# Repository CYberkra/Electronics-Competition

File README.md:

# AWG K325T — 任意波形信号发生器

> 第二十一届研电赛 · 优利德赛题二 FPGA 数字基带
> 目标器件：Xilinx Kintex-7 XC7K325TFFG900-2（正点原子 K7-325T）
> 子卡：FMCADDA-9250-9144 (AD9144 DAC)
> 扩展模块：KiCad PCB (ST7789 LCD + EC11 编码器 + Logo 丝印)

---

## 项目简介

基于 **K7-325T** + **AD9144 DAC** 的高速任意波形发生器，TX-only 纯信号生成设计。

### 核心指标

| 指标 | 值 | 赛题要求 |
|------|----|---------|
| DAC | AD9144, 4ch 16bit, 2.8Gsps | ≥5GSa/s ⚠️ |
| 垂直分辨率 | 16 bit | ≥14bit ✅ |
| 频率分辨率 | 48bit DDS, ~μHz | ≤1mHz ✅ |
| JESD204B | TX 4L @10Gbps | — |
| 时钟 | LMK04828 (50M TCXO) | — |
| 控制 | UART 115200 + 按键 | — |

### 实测幅度 (2026-06-14, 满幅度 0x7FFF)

| 100kHz | 1MHz | 10MHz | 100MHz | 300MHz |
|--------|------|-------|--------|--------|
| 60mV | 120mV | 500mV | 680mV | 470mV |

### 频谱仪频域测试 (2026-06-16, 满幅度 0x7FFF)

| 指标 | 赛题要求 | 实测值 | 结果 |
|------|----------|--------|:--:|
| 谐波失真 (100MHz) | < -40 dBc | **-54.9 dBc** | ✅ |
| 带内平坦度 (10~300MHz) | < 3 dB | **2.6 dB** | ✅ |
| 线性扫频 (10~100MHz) | 支持 | 10 峰等间距 | ✅ |
| 对数扫频 (1~128MHz) | 支持 | 8 峰倍频程 | ✅ |

### 当前进度

- [x] JESD204B 4L @10Gbps 建链
- [x] LMK04828 SPI 时钟配置
- [x] SPI clock-enable 重构 (derived clock → clk_in + spi_tick)
- [x] DDS 4级流水线 (48bit, 4采样/周期, Sine LUT 4096×16bit)
- [x] 4种波形 (正弦/方波/三角/锯齿) + BRAM 任意波形
- [x] 扫频引擎 (线性 + 对数, sweep_engine.v)
- [x] SFCW/对数扫频寄存器 (0x50-0x6C) + FMCW chirp 模式
- [x] 幅度/偏置 Q1.15 缩放
- [x] 数字校准表实例化 (ad9144_awg_cal, BRAM 16bin 频率补偿)
- [x] UART 远程控制 (115200 8N1 ASCII 协议)
- [x] 板载按键控制 (KEY0/KEY1)
- [x] KiCad 扩展模块 (ST7789 + EC11, 含 Logo 丝印)
- [x] 竞赛文档 (设计文档 + 测试方案 + PPT)
- [x] EC11 FPGA 驱动 (正交解码 + 消抖 + AWG 桥接)
- [x] ST7789 FPGA 驱动 (SPI 驱动 + 字符渲染 + 菜单系统)
- [x] 频谱仪频域测试 (谐波失真 -54.9dBc, 平坦度 2.6dB)
- [ ] 外部放大器 (→3Vpp)
- [ ] TFT/EC11 上板验证 (PCB 物理问题待排查)

---

## 环境要求

| 项目 | 版本/路径 |
|------|----------|
| **Vivado** | **2024.1** (2024.2+ 无 7 系 JESD IP) |
| 目标器件 | `xc7k325tffg900-2` |
| License | Synthesis + JESD204 |

---

## 快速开始

### 构建 & 烧录

```powershell
# 综合 → 实现 → Bitstream
& D:\Xilinx\Vivado\2024.1\bin\vivado.bat -mode batch -source scripts/build_all.tcl

# 烧录
& D:\Xilinx\Vivado\2024.1\bin\vivado.bat -mode batch -source scripts/program.tcl
```

### UART 控制

```python
python tools/set_freq.py 50000000  # 50MHz
# 或手动: W 08 00000003 (开控制) → W 10/14 (设频率) → W 2C 00000001 (应用)
```

---

## 仓库结构

```
Electronics-Competition/
├── rtl/               # Verilog RTL (top/ control/ dds/ dsp/ jesd/ sweep/ wave/)
├── constraints/       # XDC 约束 (awg_k325t.xdc, fmc_adda.xdc)
├── vivado/            # Vivado 工程
├── docs/tasks/        # 开发任务文档 (SFCW, GUI)
├── scripts/           # Tcl 构建/烧录脚本
├── tools/             # Python UART 工具
├── docs/competition/  # 竞赛文档 (设计文档/测试方案/PPT/视频脚本)
├── sim/               # 仿真 testbench
└── kicad/             # KiCad 扩展模块 PCB
```

## 扩展模块管脚

| 功能 | FPGA 引脚 | 备注 |
|------|----------|------|
| TFT SPI (6pin) | N27/M24/M27/M25/N29/M20 | ST7789, P2 CMOS接口 |
| EC11 编码器 | L20/J21/J22 | CMOS_D1/D2/D3 |
| LEDK | L30 | CMOS_D4 |

约束已备注释在 `constraints/awg_k325t.xdc` §14，顶层端口待加。

---

## 关键文档

| 需求 | 位置 |
|------|------|
| 赛题原文 (官方PDF) | `docs/references/研电赛第21届技术竞赛赛题清单.pdf` |
| 赛题原文 (文本) | `docs/competition/uni-trend-problem-statement.md` |
| 设计文档 | `docs/competition/design_document.md` |
| 测试方案 | `docs/competition/AWG指标测试方案.md` |
| 测试记录 | `docs/competition/AWG指标测试结果记录.md` |
| 答辩 PPT | `docs/competition/竞赛答辩PPT.pptx` |
| PPT 大纲 | `docs/competition/答辩PPT内容大纲.md` |
| 视频脚本 | `docs/competition/video_script.md` |
| 技术论文 | `docs/competition/技术论文.md` |
| 交付物清单 | `docs/competition/交付物清单.md` |
| 扩展模块管脚 | `kicad/模块管脚分配表.csv` |
| SFCW/FMCW 任务 | `docs/tasks/SFCW_FMCW_波形生成任务.md` |
| TFT+EC11 GUI 任务 | `docs/tasks/TFT_Encoder_GUI_菜单系统任务.md` |

---

> **最后更新**: 2026-06-15

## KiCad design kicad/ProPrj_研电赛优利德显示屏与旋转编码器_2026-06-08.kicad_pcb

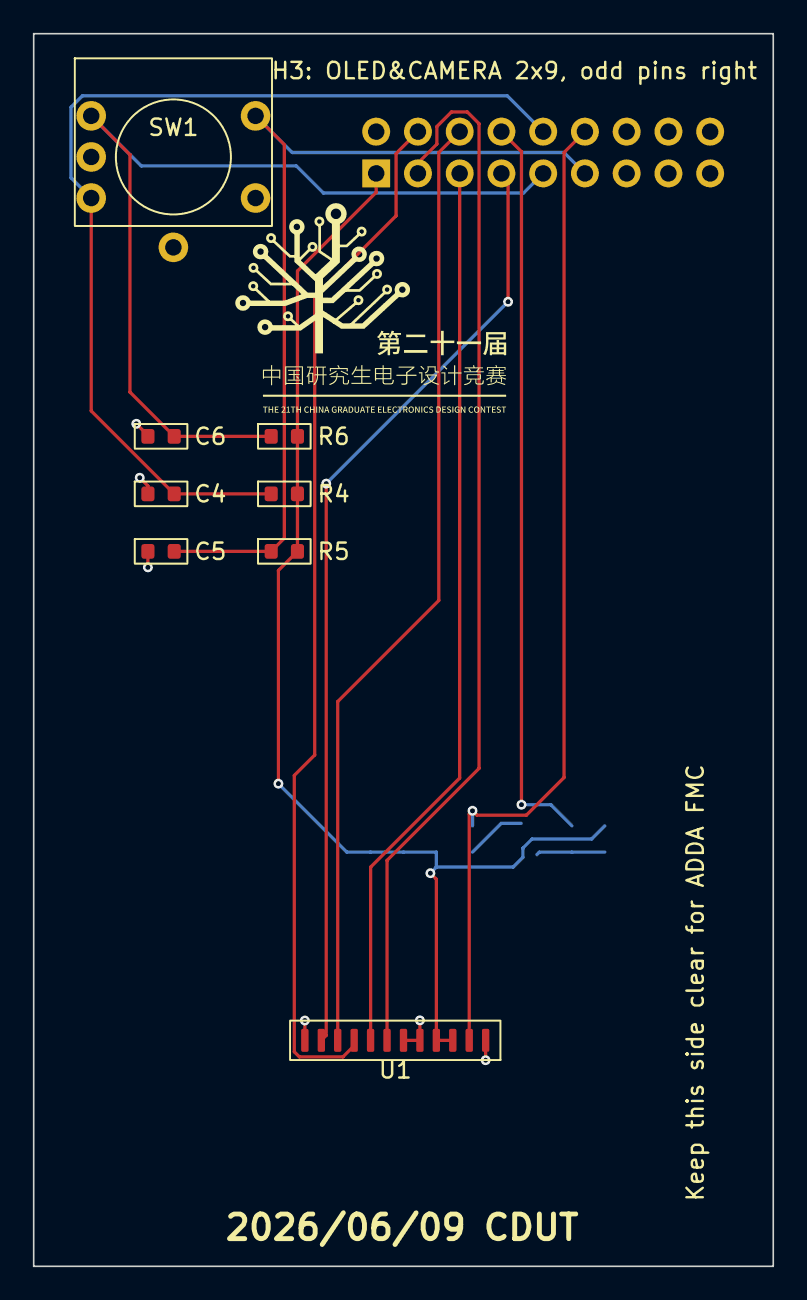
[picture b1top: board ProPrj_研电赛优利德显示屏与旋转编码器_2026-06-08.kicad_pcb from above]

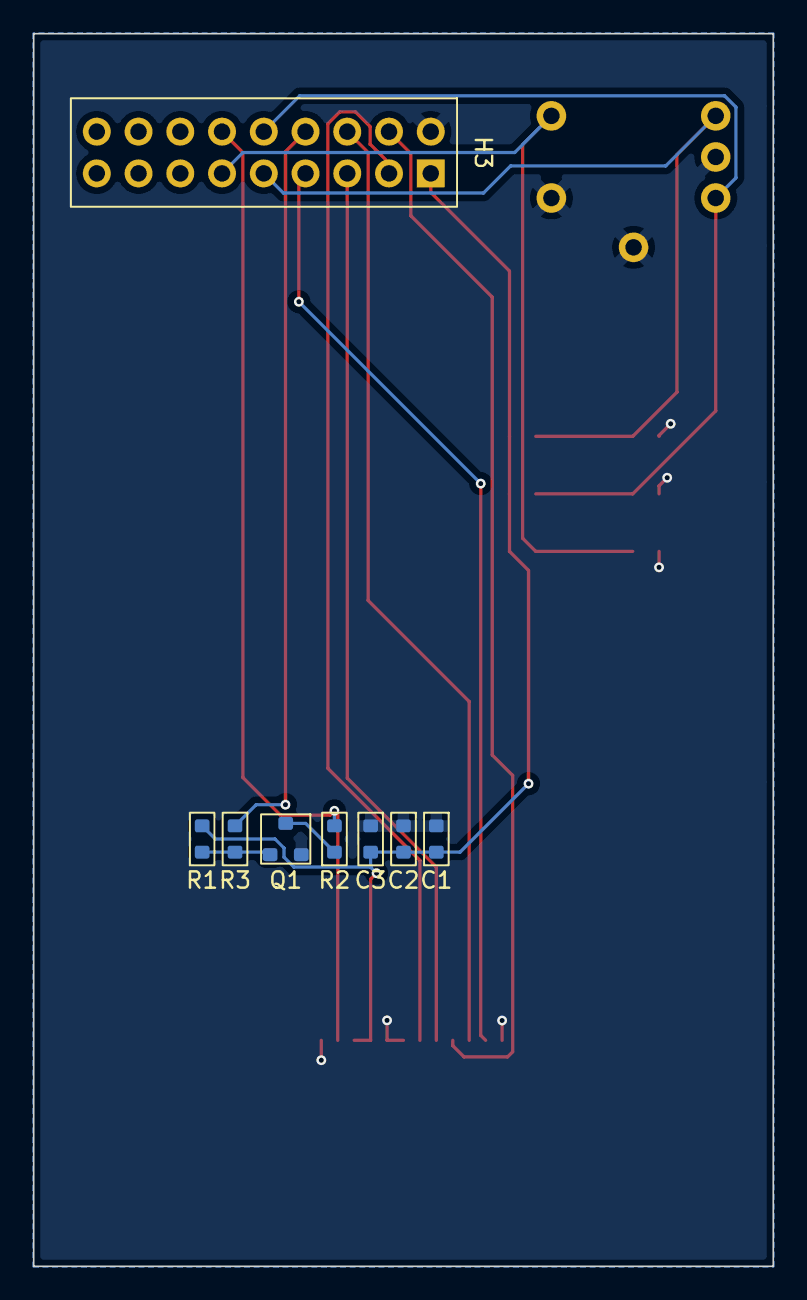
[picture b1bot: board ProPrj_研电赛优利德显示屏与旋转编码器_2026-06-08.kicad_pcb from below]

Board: 2 copper layers, 45.0 x 75.0 mm, 16 parts (8 on the bottom side), 14 nets.

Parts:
C1, C2, C3: 100nF; C0603
C4, C5, C6: 0.1uF; C0603
H3: PZ254V-12-18P; HDR-TH_18P-P2.54-V-M-R2-C9-S2.54
Q1: S8050; SOT-23-3_L2.9-W1.3-P1.90-LS2.4-BR
R1: 10k; R0603
R2: 10R; R0603
R3: 1k; R0603
R4, R5, R6: 4.7K; R0603
SW1: EC11N1525405; EC11_ROTARY_ENCODER
U1: ST7789_12P_LCD; ST7789_12P_1x12_1.00mm

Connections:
EC11-A: C6.2, H3.9, R6.1, SW1.A
EC11-B: C4.2, H3.10, R4.1, SW1.B
EC11-M: C5.2, H3.11, R5.1, SW1.D
GND: C1.1, C2.1, C3.1, C4.1, C5.1, C6.1, H3.2, Q1.2 (E), SW1.C, SW1.E, SW1.EH, U1.1, U1.5, U1.6, U1.12
LEDK: H3.12, R2.2, U1.2
unnamed: Q1.1 (B), R1.1, R3.2
unnamed: Q1.3 (C), R2.1
TFT_BLK: H3.8, R3.1
TFT_CS: H3.5, U1.8
TFT_DC: H3.3, U1.7
TFT_RES: H3.7, U1.11
TFT_SCL: H3.4, U1.9
TFT_SDA: H3.6, U1.10
VCC: C1.2, C2.2, C3.2, H3.1, R1.2, R4.2, R5.2, R6.2, U1.3, U1.4

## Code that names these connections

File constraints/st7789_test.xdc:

# ST7789 test top constraints — minimal pin set
# Board clock (100MHz differential)
set_property PACKAGE_PIN AE10 [get_ports sys_clk_p]
set_property PACKAGE_PIN AF10 [get_ports sys_clk_n]
set_property IOSTANDARD DIFF_SSTL15 [get_ports sys_clk_p]
set_property IOSTANDARD DIFF_SSTL15 [get_ports sys_clk_n]

# Reset
set_property PACKAGE_PIN AB25 [get_ports sys_rst_n]
set_property IOSTANDARD LVCMOS25 [get_ports sys_rst_n]

# ST7789 TFT (P2 CMOS/CAMERA interface)
set_property PACKAGE_PIN N27 [get_ports tft_dc]
set_property PACKAGE_PIN M24 [get_ports tft_scl]
set_property PACKAGE_PIN M27 [get_ports tft_cs]
set_property PACKAGE_PIN M25 [get_ports tft_sda]
set_property PACKAGE_PIN N29 [get_ports tft_res]
set_property PACKAGE_PIN M20 [get_ports tft_blk]
set_property IOSTANDARD LVCMOS33 [get_ports {tft_dc tft_scl tft_cs tft_sda tft_res tft_blk}]

# LED (use LED1 for test status — avoids conflict with LED0)
set_property PACKAGE_PIN R23 [get_ports test_led]
set_property IOSTANDARD LVCMOS33 [get_ports test_led]

# Clocks
create_clock -period 10.0 -name sys_clk [get_ports sys_clk_p]
set_property CONFIG_VOLTAGE 3.3 [current_design]
set_property CFGBVS VCCO [current_design]

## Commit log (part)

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2026-05-05 feat: Add FMC ADDA skeleton framework (AD9144 + AD9250)
    - Add awg_fmc_adda_top.v: top-level with all FMC HPC ports declared
    - Add ad9144_spi_ctrl.v: SPI config sequencer for AD9144
    - Add fmc_adda.xdc: constraint template with TBD placeholders
    - Create rtl/jesd/ and rtl/clk/ directories for future IP integration
    - Update .gitignore to exclude Vivado wave configs and sim outputs
2026-05-05 docs: Add AGENTS.md project knowledge base
    Include full agent guidance for K325T board, Vivado workflow,
    pin reference, and development rules for the AWG project.
2026-05-05 feat: Add LMK04828 SPI controller and JESD204 IP creation scripts (Vivado 2024.2 baseline)
    - Add lmk04828_spi_ctrl.v for clock chip configuration
    - Integrate LMK SPI into awg_fmc_adda_top.v
    - Add check_ip_version.tcl and create_jesd204_ip.tcl
    - Snapshot before migrating to Vivado 2024.1 for 7-series JESD204 support
2026-05-05 feat: Add Vivado 2024.1 migration scripts
    - upgrade_ip.tcl: Auto-upgrade IPs when opening 2024.2 project in 2024.1
    - verify_license.tcl: Verify K325T device support and JESD204 IP availability
    - create_jesd204_tx_ip.tcl: Create JESD204 TX IP for AD9144 (4-lane, 10Gbps)
    - open_project_2024.1.bat: Quick launcher for Vivado 2024.1
2026-05-05 docs: Add Obsidian knowledge base for AWG FPGA project
    - Project overview, hardware platform, toolchain
    - System architecture (top-level, clock tree, data flow)
    - Module design notes (DDS, JESD204, LMK04828)
    - Development roadmap, completed tasks, TODO list
    - Quick reference for JESD204 parameters and pin mappings
2026-05-06 refactor: make all scripts portable with relative paths + add README
    - Replace all hardcoded D:/awg_fpga absolute paths with relative path derivation
    - Tcl: [info script] + [file normalize]
    - Python: Path(__file__).parent.resolve()
    - PowerShell: $MyInvocation.MyCommand.Path
    - Batch: %~dp0
    - Cover old scripts and upstream-added scripts (vivado2024.1/)
2026-05-06 feat: add AWG key UI control and teaching DAC constraints
2026-05-06 docs: record AWG debug observability status
2026-05-06 docs: update AWG debug capture status
2026-05-06 fix: stabilize AD9144 button waveform stepping
2026-05-06 Add BRAM waveform and sweep modes to AWG core
2026-05-06 feat: add AD9144 waveform button mode
2026-05-06 docs: record AD9144 waveform demo baseline
2026-05-06 feat: add AD9144 AWG register debug path
2026-05-06 docs: mark UART control plan complete
2026-05-07 docs: record UART board check
2026-05-07 docs: record UART panel workflow
2026-05-07 docs: record UART sweep logger
2026-05-07 docs: mark AWG GUI sweep plan complete
2026-05-07 feat: add AWG scope measurement workflow
2026-05-07 refactor: replace all hardcoded D:/awg_fpga and D:/FPGA paths with relative paths
    Makes the repo portable - can be cloned to any directory.
    Changes:
    - All Tcl scripts now derive repo root from [info script]
    - ad9144_bringup_k325t scripts derive bringup root relative to script dir
    - RTL: ad9144_awg_dds4.v INIT_FILE parameter made relative
    - README.md: commands use relative paths and VIVADO_PATH env var
2026-05-07 refactor: replace remaining hardcoded paths in active scripts and tools
    Second batch of path fixes:
    Root-level scripts:
    - build_key_freq.tcl
    - scripts/program_latest_awg_bit.tcl
    - scripts/create_project.tcl
    - scripts/create_project_and_ip.tcl
2026-05-08 feat: complete AD9144 UART bitstream with calibration module
2026-05-09 docs: correct KiCad progress to reflect actual schematic state
2026-05-10 chore: clean PR3 text whitespace
2026-05-10 chore: normalize PR3 text endings
2026-05-10 feat: add fixed-hardware competition demo package
2026-05-10 feat: add calibration table tooling
2026-05-11 Add PySide6 upper-host application
2026-05-14 test: add upper host smoke checks
2026-05-16 docs: add competition completion optimization plan
2026-05-16 test: add project health gate
2026-06-09 chore: add vivado PID file to gitignore
    Ignore vivado_pid*.str temporary process files created by Vivado
2026-06-09 chore: ignore KiCad generated files
2026-06-09 chore: ignore .Xil Vivado cache directory
